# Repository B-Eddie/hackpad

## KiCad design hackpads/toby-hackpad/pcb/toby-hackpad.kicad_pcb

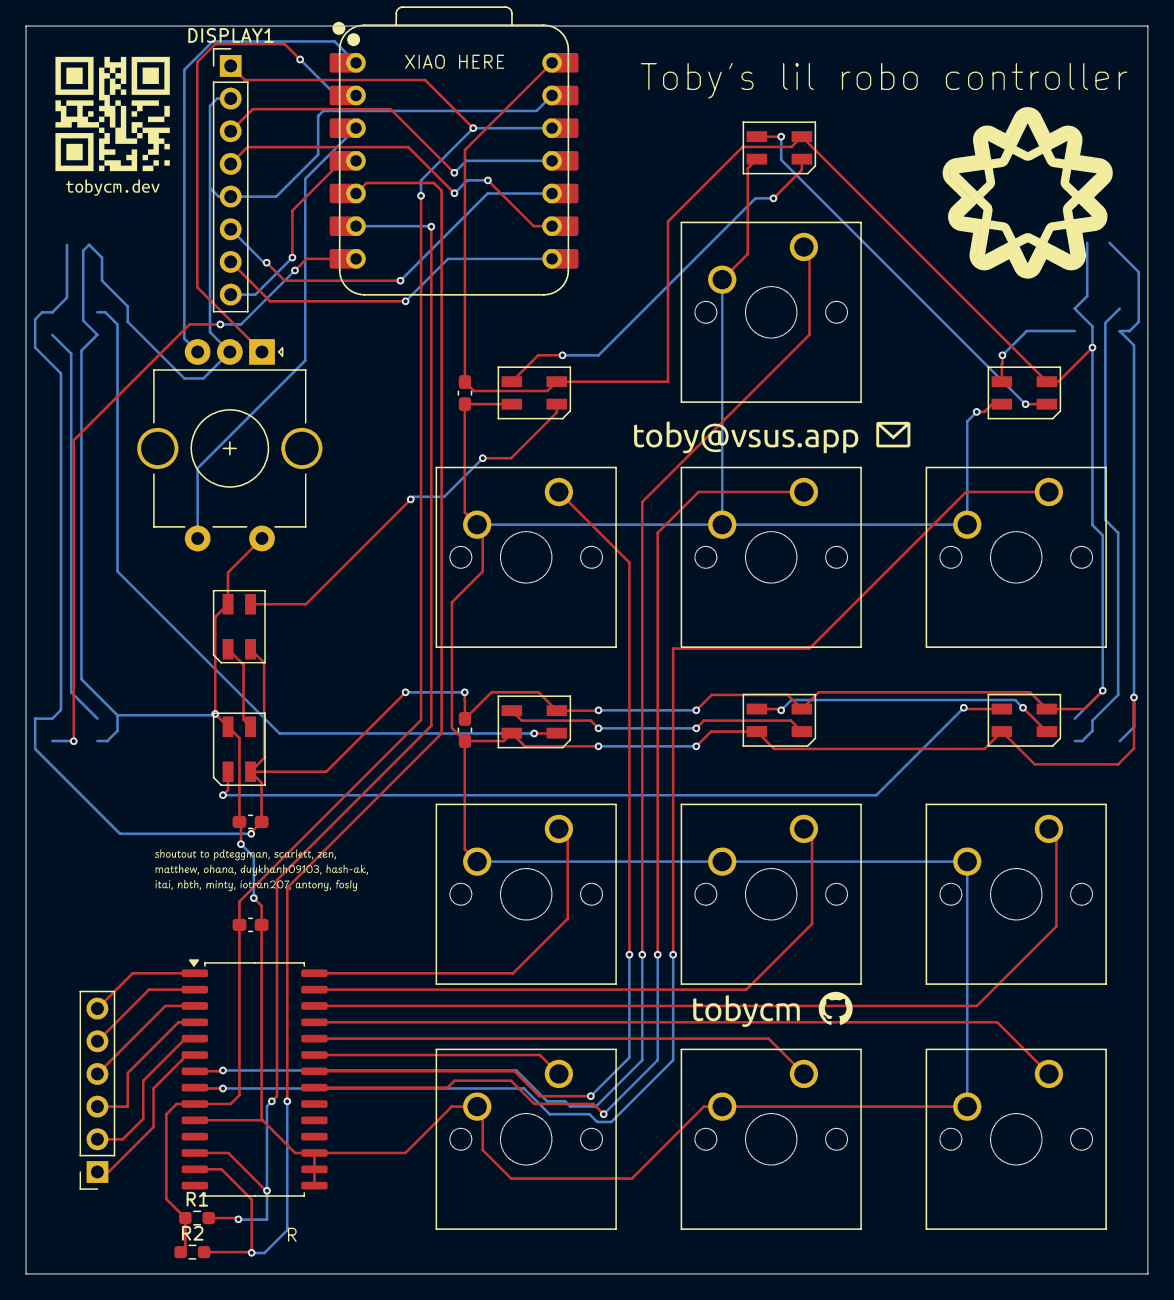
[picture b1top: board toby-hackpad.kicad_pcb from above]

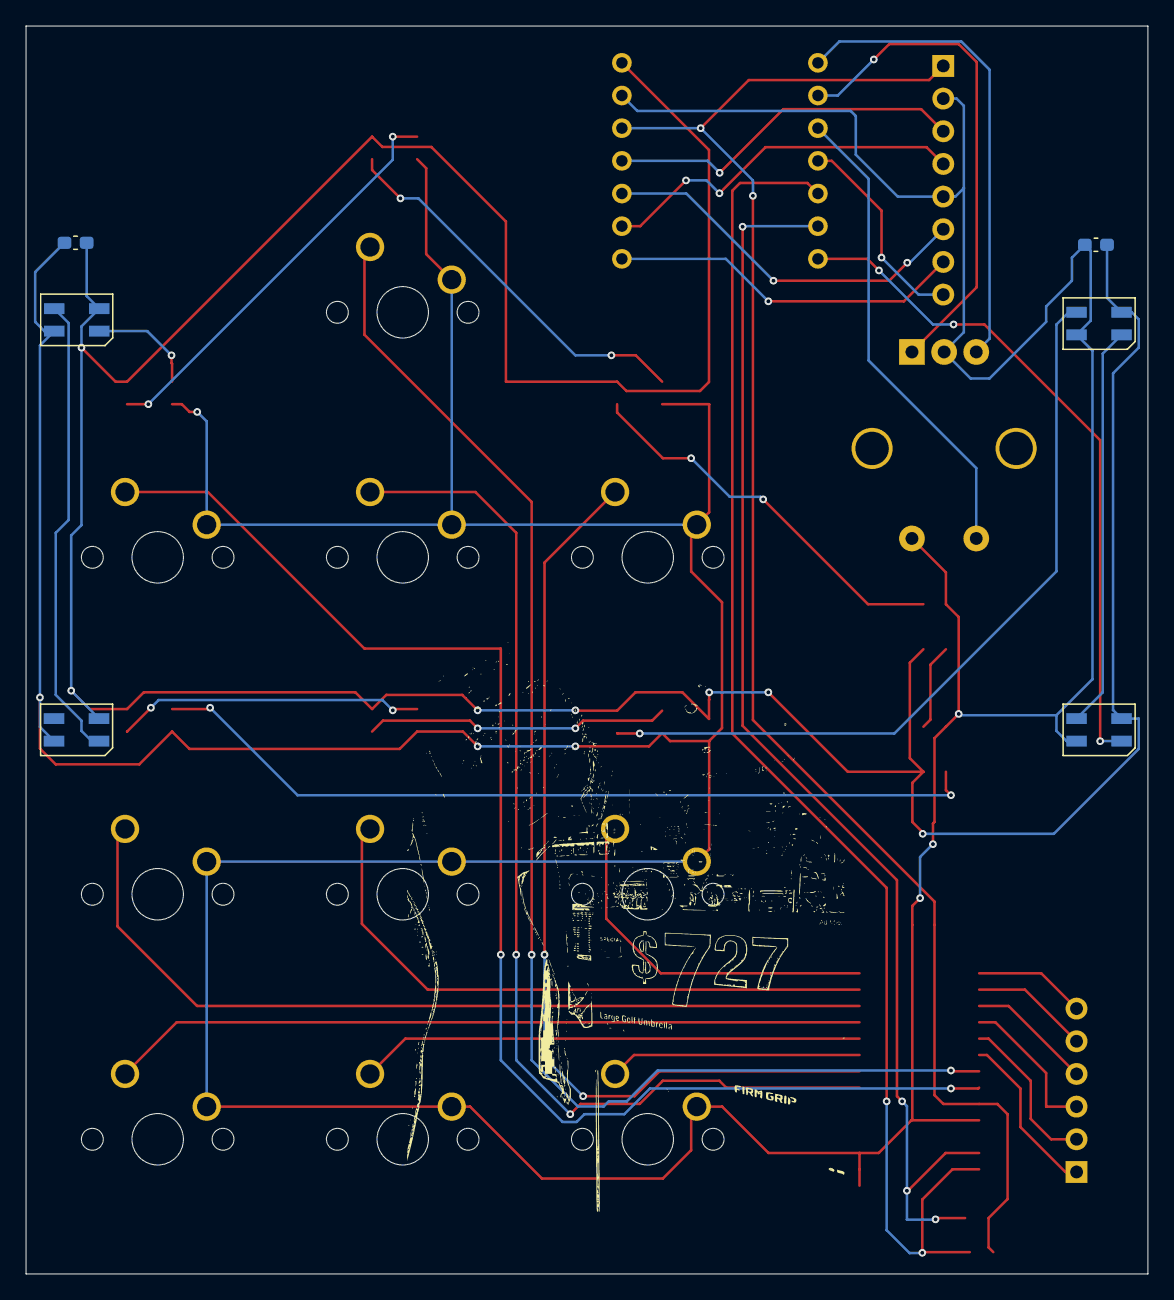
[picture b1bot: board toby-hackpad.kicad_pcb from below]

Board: 2 copper layers, 87.2 x 97.0 mm, 35 parts (6 on the bottom side), 41 nets.

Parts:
C1, C3, C4, C5, C6: 1uF; C_0603_1608Metric_Pad1.08x0.95mm_HandSolder
C2: 100nF; C_0603_1608Metric_Pad1.08x0.95mm_HandSolder
D1, D2, D3, D4, D5, D6, D7, D8, D9, D10, D11, D12: SK6812MINI; LED_SK6812MINI_PLCC4_3.5x3.5mm_P1.75mm
DISPLAY1: PinHeader_1x08_P2.54mm_Vertical
J1: Conn_01x06_Pin; PinSocket_1x06_P2.54mm_Vertical
R1, R2: 4.7K; R_0603_1608Metric_Pad0.98x0.95mm_HandSolder
SW1, SW2, SW3, SW4, SW5, SW6, SW7, SW8, SW9, SW10: SW_Push; SW_Cherry_MX_1.00u_PCB
SW11: RotaryEncoder_Switch; RotaryEncoder_Alps_EC11E-Switch_Vertical_H20mm_CircularMoun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
U1: XIAO-RP2040-DIP
U2: MCP23017_SO; SOIC-28W_7.5x17.9mm_P1.27mm

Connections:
+3.3V: C2.2, DISPLAY1.1 (VCC), R1.1, R2.1, U1.12 (3V3), U2.9 (VDD)
+5V: C1.1, C3.1, C4.1, C5.1, C6.1, D1.4 (VDD), D2.4 (VDD), D3.4 (VDD), D4.4 (VDD), D5.4 (VDD), D6.4 (VDD), D7.4 (VDD), D8.4 (VDD), D9.4 (VDD), D10.4 (VDD), D11.4 (VDD), D12.4 (VDD), U1.14 (VBUS)
GND: C1.2, C2.1, C3.2, C4.2, C5.2, C6.2, D1.2 (VSS), D2.2 (VSS), D3.2 (VSS), D4.2 (VSS), D5.2 (VSS), D6.2 (VSS), D7.2 (VSS), D8.2 (VSS), D9.2 (VSS), D10.2 (VSS), D11.2 (VSS), D12.2 (VSS), DISPLAY1.2 (GND), DISPLAY1.5 (CS), SW1.2, SW2.2, SW3.2, SW4.2, SW5.2, SW6.2, SW7.2, SW8.2, SW9.2, SW10.2, SW11.C, SW11.S2, U1.13 (GND), U2.10 (VSS), U2.15 (A0), U2.16 (A1), U2.17 (A2)
unnamed: D1.3 (DIN), U1.7 (GPIO0/TX)
unnamed: D1.1 (DOUT), D2.3 (DIN)
unnamed: D2.1 (DOUT), D7.3 (DIN)
unnamed: D3.1 (DOUT), D4.3 (DIN)
unnamed: D5.3 (DIN), D9.1 (DOUT)
unnamed: D5.1 (DOUT), D6.3 (DIN)
unnamed: D7.1 (DOUT), D8.3 (DIN)
unnamed: D8.1 (DOUT), D9.3 (DIN)
unnamed: D6.1 (DOUT), D10.3 (DIN)
unnamed: D10.1 (DOUT), D11.3 (DIN)
unnamed: D11.1 (DOUT), D12.3 (DIN)
unnamed: D3.3 (DIN), D12.1 (DOUT)
unnamed: DISPLAY1.8 (BL), U1.4 (GPIO29/ADC3/A3)
unnamed: DISPLAY1.4 (CLK), U1.9 (GPIO2/SCK)
unnamed: DISPLAY1.6 (DC), U1.10 (GPIO4/MISO)
unnamed: DISPLAY1.3 (DIN), U1.11 (GPIO3/MOSI)
unnamed: DISPLAY1.7 (RST), U1.8 (GPIO1/RX)
unnamed: J1.1, U2.6 (GPB5)
unnamed: J1.2, U2.5 (GPB4)
unnamed: J1.3, U2.4 (GPB3)
unnamed: J1.4, U2.3 (GPB2)
unnamed: J1.5, U2.2 (GPB1)
unnamed: J1.6, U2.1 (GPB0)
unnamed: R2.2, U1.5 (GPIO6/SDA), U2.13 (SDA)
unnamed: R1.2, U1.6 (GPIO7/SCL), U2.12 (SCK)
unnamed: SW11.B, U1.1 (GPIO26/ADC0/A0)
unnamed: SW11.A, U1.2 (GPIO27/ADC1/A1)
unnamed: SW11.S1, U1.3 (GPIO28/ADC2/A2)
unnamed: SW8.1, U2.21 (GPA0)
unnamed: SW7.1, U2.22 (GPA1)
unnamed: SW6.1, U2.23 (GPA2)
unnamed: SW5.1, U2.24 (GPA3)
unnamed: SW4.1, U2.25 (GPA4)
unnamed: SW2.1, U2.26 (GPA5)
unnamed: SW3.1, U2.27 (GPA6)
unnamed: SW1.1, U2.28 (GPA7)
unnamed: SW9.1, U2.7 (GPB6)
unnamed: SW10.1, U2.8 (GPB7)
